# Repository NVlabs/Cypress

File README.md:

# Cypress: VLSI-Inspired Scalable GPU-Accelerated PCB Placement

Cypress is a scalable, GPU-accelerated PCB placement method inspired by VLSI. It incorporates
tailored cost functions, constraint handling, and optimized techniques adapted for PCB layouts.

## How to Build

You can build in two ways:

- Build without Docker by following the instructions of the DREAMPlace build at README_DREAMPlace.md.
- Use the provided Dockerfile to build an image with the required library dependencies.

## Run PCB Placement

```sh
cd /Cypress
python dreamplace/Placer.py path/to/your/config.json
```

## Run Hyperparameter search

```sh
./tuner/run_tuner.sh 1 1 	test/tune/pcb-configspace.json 	/path/to/aux_file 	test/tuner/tuner-ppa.json "" 	100 4 0 0 10 	./tuner 	./results/result_path
```

## Acknowledgement

Cypress builds upon and extends the following open-source projects:

- [DREAMPlace](https://github.com/limbo018/DREAMPlace): A deep learning toolkit-enabled VLSI placement framework that provides the foundation for our GPU-accelerated placement engine.

- [AutoDMP](https://github.com/NVlabs/AutoDMP): An automated design methodology platform that inspired aspects of our hyperparameter tuning approach.

We thank the authors and contributors of these projects for their valuable work that made Cypress possible.

## Citation

If you find this work useful, please cite the following paper:

```bibtex
@inproceedings{zhang2025cypress,
  title={Cypress: VLSI-Inspired PCB Placement with GPU Acceleration},
  author={Zhang, Niansong and Agnesina, Anthony and Shbat, Noor and Leader, Yuval and Zhang, Zhiru and Ren, Haoxing},
  booktitle={Proceedings of the 2025 International Symposium on Physical Design},
  pages={xx--xx},
  year={2025}
}
```

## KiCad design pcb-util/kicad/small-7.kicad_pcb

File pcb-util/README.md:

# pcb-util

## Getting started

To make it easy for you to get started with GitLab, here's a list of recommended next steps.

Already a pro? Just edit this README.md and make it your own. Want to make it easy? [Use the template at the bottom](#editing-this-readme)!

## Add your files

- [ ] [Create](https://docs.gitlab.com/ee/user/project/repository/web_editor.html#create-a-file) or [upload](https://docs.gitlab.com/ee/user/project/repository/web_editor.html#upload-a-file) files
- [ ] [Add files using the command line](https://docs.gitlab.com/ee/gitlab-basics/add-file.html#add-a-file-using-the-command-line) or push an existing Git repository with the following command:

```
cd existing_repo
git remote add origin https://gitlab-master.nvidia.com/niansongz/pcb-util.git
git branch -M main
git push -uf origin main
```

## Integrate with your tools

- [ ] [Set up project integrations](https://gitlab-master.nvidia.com/niansongz/pcb-util/-/settings/integrations)

## Collaborate with your team

- [ ] [Invite team members and collaborators](https://docs.gitlab.com/ee/user/project/members/)
- [ ] [Create a new merge request](https://docs.gitlab.com/ee/user/project/merge_requests/creating_merge_requests.html)
- [ ] [Automatically close issues from merge requests](https://docs.gitlab.com/ee/user/project/issues/managing_issues.html#closing-issues-automatically)
- [ ] [Enable merge request approvals](https://docs.gitlab.com/ee/user/project/merge_requests/approvals/)
- [ ] [Set auto-merge](https://docs.gitlab.com/ee/user/project/merge_requests/merge_when_pipeline_succeeds.html)

## Test and Deploy

Use the built-in continuous integration in GitLab.

- [ ] [Get started with GitLab CI/CD](https://docs.gitlab.com/ee/ci/quick_start/index.html)
- [ ] [Analyze your code for known vulnerabilities with Static Application Security Testing (SAST)](https://docs.gitlab.com/ee/user/application_security/sast/)
- [ ] [Deploy to Kubernetes, Amazon EC2, or Amazon ECS using Auto Deploy](https://docs.gitlab.com/ee/topics/autodevops/requirements.html)
- [ ] [Use pull-based deployments for improved Kubernetes management](https://docs.gitlab.com/ee/user/clusters/agent/)
- [ ] [Set up protected environments](https://docs.gitlab.com/ee/ci/environments/protected_environments.html)

***

# Editing this README

When you're ready to make this README your own, just edit this file and use the handy template below (or feel free to structure it however you want - this is just a starting point!). Thanks to [makeareadme.com](https://www.makeareadme.com/) for this template.

## Suggestions for a good README

Every project is different, so consider which of these sections apply to yours. The sections used in the template are suggestions for most open source projects. Also keep in mind that while a README can be too long and detailed, too long is better than too short. If you think your README is too long, consider utilizing another form of documentation rather than cutting out information.

## Name
Choose a self-explaining name for your project.

## Description
Let people know what your project can do specifically. Provide context and add a link to any reference visitors might be unfamiliar with. A list of Features or a Background subsection can also be added here. If there are alternatives to your project, this is a good place to list differentiating factors.

## Badges
On some READMEs, you may see small images that convey metadata, such as whether or not all the tests are passing for the project. You can use Shields to add some to your README. Many services also have instructions for adding a badge.

## Visuals
Depending on what you are making, it can be a good idea to include screenshots or even a video (you'll frequently see GIFs rather than actual videos). Tools like ttygif can help, but check out Asciinema for a more sophisticated method.

## Installation
Within a particular ecosystem, there may be a common way of installing things, such as using Yarn, NuGet, or Homebrew. However, consider the possibility that whoever is reading your README is a novice and would like more guidance. Listing specific steps helps remove ambiguity and gets people to using your project as quickly as possible. If it only runs in a specific context like a particular programming language version or operating system or has dependencies that have to be installed manually, also add a Requirements subsection.

## Usage
Use examples liberally, and show the expected output if you can. It's helpful to have inline the smallest example of usage that you can demonstrate, while providing links to more sophisticated examples if they are too long to reasonably include in the README.

## Support
Tell people where they can go to for help. It can be any combination of an issue tracker, a chat room, an email address, etc.

## Roadmap
If you have ideas for releases in the future, it is a good idea to list them in the README.

## Contributing
State if you are open to contributions and what your requirements are for accepting them.

For people who want to make changes to your project, it's helpful to have some documentation on how to get started. Perhaps there is a script that they should run or some environment variables that they need to set. Make these steps explicit. These instructions could also be useful to your future self.

You can also document commands to lint the code or run tests. These steps help to ensure high code quality and reduce the likelihood that the changes inadvertently break something. Having instructions for running tests is especially helpful if it requires external setup, such as starting a Selenium server for testing in a browser.

## Authors and acknowledgment
Show your appreciation to those who have contributed to the project.

## License
For open source projects, say how it is licensed.

## Project status
If you have run out of energy or time for your project, put a note at the top of the README saying that development has slowed down or stopped completely. Someone may choose to fork your project or volunteer to step in as a maintainer or owner, allowing your project to keep going. You can also make an explicit request for maintainers.

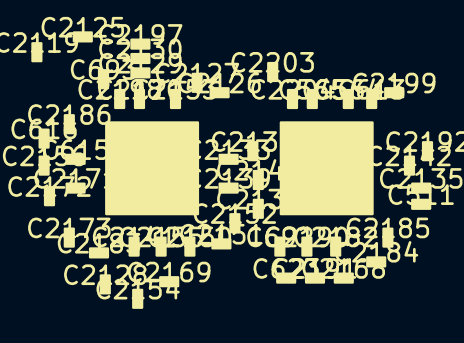
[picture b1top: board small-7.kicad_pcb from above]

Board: 2 copper layers, 52 parts (0 on the bottom side), 44 nets, no tracks yet.

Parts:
C448: C448
C449: C449
C511: C511
C564: C564
C565: C565
C613: C613
C615: C615
C616: C616
C623: C623
C692: C692
C693: C693
C2119: C2119
C2125: C2125
C2126: C2126
C2127: C2127
C2128: C2128
C2129: C2129
C2130: C2130
C2133: C2133
C2134: C2134
C2135: C2135
C2138: C2138
C2139: C2139
C2140: C2140
C2141: C2141
C2142: C2142
C2150: C2150
C2151: C2151
C2152: C2152
C2153: C2153
C2154: C2154
C2155: C2155
C2156: C2156
C2168: C2168
C2169: C2169
C2170: C2170
C2171: C2171
C2172: C2172
C2173: C2173
C2182: C2182
C2183: C2183
C2184: C2184
C2185: C2185
C2186: C2186
C2190: C2190
C2191: C2191
C2192: C2192
C2197: C2197
C2198: C2198
C2199: C2199
C2203: C2203
C2204: C2204

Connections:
N45: C448.0, C448.1, C449.0, C449.1, C564.0, C565.0, C2119.0, C2125.0, C2129.0, C2153.0, C2170.0, C2198.0, C2204.0
N73: C449.2, C2197.0, C2198.1
N74: C448.2, C2203.0, C2204.1
N431: C449.3, C615.1
N452: C449.4, C616.1
N456: C448.3, C613.1
N501: C448.4, C449.5, C2129.1, C2130.1
N526: C448.5, C2199.1
N528: C448.6, C2192.1
N536: C448.7, C2142.1
N538: C448.8, C2135.1
N1836: C448.9, C449.6, C2125.1
N1837: C448.10, C449.7, C2119.1
N4122: C449.9, C2128.1
N4129: C448.22, C511.1
N4139: C449.10, C2155.1
N4163: C449.11, C2169.1
N4172: C449.12, C2171.1
N4179: C449.13, C2156.1
N4187: C449.14, C2154.1
N4196: C449.15, C2141.1
N4213: C449.16, C693.1
N4215: C448.23, C692.1
N4231: C449.17, C2186.1
N4233: C448.24, C623.1
N4244: C448.25, C2191.1
N4247: C448.26, C2185.1
N4250: C448.27, C2168.1
N4258: C448.28, C2190.1
N4261: C448.29, C2184.1
N4264: C448.30, C2182.1
N4303: C449.18, C2133.1
N4308: C449.19, C2151.1
N4313: C449.20, C2140.1
N4318: C449.21, C2150.1
N4383: C449.22, C2126.1
N4388: C449.23, C2138.1
N4393: C449.24, C2134.1
N4398: C449.25, C2152.1
N4427: C449.26, C2183.0
N4586: C449.27, C2127.1
N4591: C449.28, C2139.1
N4651: C449.29, C2173.1
N4660: C449.30, C2172.1

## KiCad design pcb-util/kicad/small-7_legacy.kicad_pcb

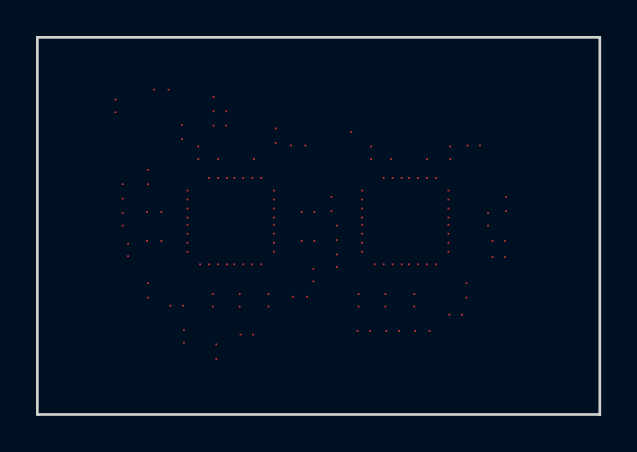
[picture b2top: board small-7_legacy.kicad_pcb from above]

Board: 2 copper layers, 31.2 x 21.0 mm, 52 parts (0 on the bottom side), 44 nets, no tracks yet.

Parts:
C0: C0; C2153
C1: C1; C2170
C2: C2; C564
C3: C3; C565
C4: C4; C693
C5: C5; C2186
C6: C6; C2173
C7: C7; C2172
C8: C8; C2171
C9: C9; C2156
C10: C10; C2155
C11: C11; C2154
C12: C12; C2141
C13: C13; C2128
C14: C14; C615
C15: C15; C616
C16: C16; C623
C17: C17; C692
C18: C18; C613
C19: C19; C511
C20: C20; C2204
C21: C21; C2203
C22: C22; C2198
C23: C23; C2197
C24: C24; C2125
C25: C25; C2119
C26: C26; C2130
C27: C27; C2129
C28: C28; C2199
C29: C29; C2192
C30: C30; C2142
C31: C31; C2135
C32: C32; C2169
C33: C33; C2168
C34: C34; C2182
C35: C35; C2127
C36: C36; C2126
C37: C37; C2134
C38: C38; C2133
C39: C39; C2140
C40: C40; C2139
C41: C41; C2138
C42: C42; C2152
C43: C43; C2151
C44: C44; C2150
C45: C45; C2185
C46: C46; C2184
C47: C47; C2183
C48: C48; C2191
C49: C49; C2190
C50: C50; C448
C51: C51; C449

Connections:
N45: C0.0, C1.0, C2.0, C3.0, C20.0, C22.0, C24.0, C25.0, C27.0, C50.0, C50.1, C51.0, C51.1
N73: C22.1, C23.0, C51.2
N74: C20.1, C21.0, C50.2
N431: C14.1, C51.3
N452: C15.1, C51.4
N456: C18.1, C50.3
N501: C26.1, C27.1, C50.4, C51.5
N526: C28.1, C50.5
N528: C29.1, C50.6
N536: C30.1, C50.7
N538: C31.1, C50.8
N1836: C24.1, C50.9, C51.6
N1837: C25.1, C50.10, C51.7
N4122: C13.1, C51.9
N4129: C19.1, C50.22
N4139: C10.1, C51.10
N4163: C32.1, C51.11
N4172: C8.1, C51.12
N4179: C9.1, C51.13
N4187: C11.1, C51.14
N4196: C12.1, C51.15
N4213: C4.1, C51.16
N4215: C17.1, C50.23
N4231: C5.1, C51.17
N4233: C16.1, C50.24
N4244: C48.1, C50.25
N4247: C45.1, C50.26
N4250: C33.1, C50.27
N4258: C49.1, C50.28
N4261: C46.1, C50.29
N4264: C34.1, C50.30
N4303: C38.1, C51.18
N4308: C43.1, C51.19
N4313: C39.1, C51.20
N4318: C44.1, C51.21
N4383: C36.1, C51.22
N4388: C41.1, C51.23
N4393: C37.1, C51.24
N4398: C42.1, C51.25
N4427: C47.0, C51.26
N4586: C35.1, C51.27
N4591: C40.1, C51.28
N4651: C6.1, C51.29
N4660: C7.1, C51.30

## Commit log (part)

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2019-10-06 fix boost link in readme
2019-10-15 rename maximum independent set to maximal
2019-10-15 global swap deterministic now
2019-10-17 k reorder deterministic now; found ism is not deterministic for bigblue4
2019-10-19 add run-to-run determinism to readme
2019-10-26 change default install prefix to current_path/install
2019-10-26 clarify the run-to-run determinism is for one machine/device
2019-10-28 add dreamplace flow to readme
2019-10-28 add image
2019-11-05 early release of docker for easier compile environment
2019-11-08 support movable macros with greedy and lp based macro legalization
2019-11-08 update legalization flow figure
2019-11-08 add limits to hannan grid sizes and fix missing read_pl
2019-11-08 fix bug in macro legalization from numeric type in mcf solver and site/row misalignment in hannan grid
2019-11-15 clamp fixed density map and add more detailed debug message to cpu
2019-11-18 use exactly the same impl for fixed density map computation as cpu/cuda
2019-12-08 set numpy threading as well after reading the parameters
2019-12-10 switch to clean control over json parameters and add description to readme as well
2019-12-18 support torch 1.3.1. coauthor: Jiaqi Gu
2019-12-18 add file for rudy and adjust instance area
2019-12-21 coauthor Jiaqi Gu, tmp checkpoint
2019-12-21 fix cmake issue when no cuda available
2019-12-21 fix bug in parsing parameters
2019-12-21 make previous bug fix general to python2 and python3
2019-12-22 the area optimization can run
2019-12-22 recover node size and pin offset for legalization
2019-12-22 fix bug in reading DEF file with UNPLACED instance without ORIENT
2019-12-22 fix DEF writer and diverging issue on ISPD2015 benchmarks by scaling the site width to 1
2019-12-23 fix bug in params to get solution file format
2019-12-23 ispd2005 test JSON adds L2/L3 iterations
2019-12-24 change nonlinear place to 3-level nested problems
2019-12-24 guarantee run-to-run determinism on CPU now
2019-12-24 fix bug when regions are placed after groups in DEF
2019-12-25 track ispd2005 JSON files for adam and momentum solvers
2019-12-26 coauthor: Gu Jiaqi. finish area computations on GPU
2019-12-27 coauthor: Jiaqi Gu. add unittests for pin utilization and rudy
2019-12-28 pass AdjustNodeAreaUnittest
2019-12-28 clean adjust node area and unitest
2019-12-30 tune routability in progress
2019-12-31 weighted average wirelength CPU implementations of atomic and merged
2020-01-01 Add unittest. Improve CPU merged implementation.
2020-01-05 integrate nctugr binary for routing congestion estimation
2020-01-05 change back to call ntuplace4h
2020-01-05 Revert "resolve merge conflict"
    This reverts commit a29376cf3cd48015002ff325e95d718a6a23fe3e, reversing
    changes made to f26a3c230b7f59befb56b5053743d8bf93be6ca6.
2020-01-07 remove redundant if-else in weighted_average_wirelength
2020-01-07 remove wa wl sparse implementation
2020-01-08 remove redundant POST9 and POWV9 files for flute and NCTUgr.ICCAD2012
2020-01-08 move legality check to python operator
2020-01-08 update dac2012 json files
2020-01-08 fix compile warning in wa wl
2020-01-08 fix hard-coded gamma to JSON files
2020-01-17 fix bug in macro legalization
2020-01-19 fix bug in logsumexp wl computation
2020-01-31 add ABCDPlace paper
2020-02-06 fix macro legalization for bigblue3 when there are single-pin macros overlapping with each other
2020-02-07 rearrange code for Robert's mixed-size placement exp
2020-02-13 add a configure file to record the compile information for an installation
2020-02-13 remove depracated wa sparse
2020-03-05 add checking when target density is smaller than utilization
2020-03-18 resolve issue with boost-cmake
2020-03-19 add load function for pklz
2020-03-25 fix bug in global swap for space misalignment
2020-03-28 remove unused dependency to cusparse
2020-03-28 fix failure in regression test of adaptec2
2020-04-14 debug for inconsistent in electric_potential unittest
2020-04-14 sorted node map should only be on the movable nodes
2020-04-15 fix bug in ispd19 benchmarks with multiple sites; hotfix of divergence issue with better preconditioning, which may not be the best way
2020-04-16 separate place_io python binding into multipel files to speedup make
2020-04-17 support parallel building now
2020-04-18 replace buffer-style density map computation with fixed point numbers
2020-04-20 add regression test
2020-04-20 detect divergence and add assertion to fence regions
2020-04-29 handle non-CORE classes in LEF, regard as fixed
2020-04-29 try to match plus for this commit
2020-04-30 add regression test for iccad2014/ispd2014
2020-04-30 return metrics after finishing place for data collection
2020-05-06 fix bug for ispd2018 with numerical precision issues; we cannot legalize test10 yet, as it is too dense
2020-05-06 fix efficiency issue when wildcard matching fence regions
2020-05-07 update benchmark configuration files
2020-05-11 add upper bounds for alpha in preconditioning
2020-05-13 init commit
2020-05-13 update optimizer
2020-05-13 solve prob 2
2020-05-13 recover nonlinearplace.py
2020-05-13 bug fix
2020-05-13 bug fixed
2020-05-13 move out nonexclusive cell
2020-05-13 fix nonexclusive cell
2020-05-13 fence region update
2020-05-13 fence region exclude
2020-05-14 update fence region margin
2020-05-14 update region check
2020-05-16 quadratic and multi-electric field
2020-05-17 multi-electric field
2020-06-11 remove support to python2
2020-06-11 add ispd19 test script
2020-07-07 fix issue with DEF pins without layer and bounding box
2020-07-07 handle DEF net weighting now
2020-07-09 better check on divergence
2020-07-09 fix bug of block count overflow in density map kernel launching
2020-07-12 fix bug in inconsistent lef/def unit
2020-07-13 compile issue after merging
2020-08-10 fix bug in reading verilog modules
2020-08-27 add missing members in PlaceDB
2021-02-23 fix typo in unused build_density_overflow
2021-06-03 Update benchmarks
    Correct README and benchmark Python script
2021-06-15 FFT API compatibility for PyTorch 1.8
2021-06-15 fix CXX standard issue due to wierd cmake initialization to CMAKE_CXX_FLAGS
2021-06-17 update to torch header
2021-06-21 remove setup.py.in and use CMakeLists only
2021-06-23 Fix TARGET_NAME typo in k_reorder and comment rmst_wl
2021-06-25 DP working under PyTorch 1.8 + CUDA 11.\n Major fixes: 1. Put cub into DreamPlace namespace (following https://github.com/dmlc/dgl/pull/2758/commits/fd183c156b063c2c783e0a9d3501bce4a44f9aeb);\n 2. Re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
2021-07-02 set default detailed placer on ISPD 2005 benchmarks to ABCDPlace
2021-07-08 fix bug in cmake of pin_pos
2021-07-22 update docker configuration.
2021-08-23 node2fence region map fix
    Conflicts:
    dreamplace/ops/global_swap/src/global_swap_cuda_kernel.cu
2021-08-23 fence region legalization and legality check
    Conflicts:
    dreamplace/BasicPlace.py
2021-08-23 only abacus after one legality check
2021-08-23 fix precond bug
2021-08-23 add global overflow
2021-08-23 enlarge virtual macro dilation
2021-08-23 enable placement flag for all ispd15 and ispd19
2021-08-23 fix bug in ntuplace4dr call
2021-08-23 fix some tensor shape issue
2021-08-23 fix bug in polygen slicing
2021-08-23 quadratic penalty and alpha increase
2021-08-23 fix merge slicing bug
2021-08-23 fix bug in movable macro mask
2021-08-23 enable blockage for ISPD2015
2021-08-23 fix overflow tensor shape issue
2021-08-23 add dreamplace 2.0 paper
2021-08-28 [dreamplace3.0] update GP flow
2021-08-28 [dreamplace3.0] remove placedb usage in base_gamma
2021-08-28 [dreamplace3.0] fix fence region install bug
2021-08-28 [dreamplace3.0] ispd 2015 regression test script
2021-08-28 [dreamplace3.0] multiple runs to test sensitivity
2021-08-30 [dreamplace3.0] update shapely package
2021-08-30 [dreamplace3.0] clean comments and format
2021-08-31 update readme to include 3.0 features
2021-09-04 update dockerfiler and requirement to torch version and shapely
2022-11-17 fix bug in PlaceDB when calling dreamplacePrint
2022-11-17 fix numerical bug in abacus legalization when distributing cells into rows
2022-11-17 bin num calculate error
    ```math.ceil()``` can cause ```num_bins``` calculation errors.
2022-11-17 add heuristic to select core site when there are multiple site definitions
2022-11-17 AutoDMP dreamplace update
2022-11-17 AutoDMP tuner
2022-11-17 update requirements
2022-11-17 AutoDMP add hpbandster library
2022-11-18 update Dockerfile
2022-11-18 update dockerfile with correct torch installation
2022-11-19 Keep DREAMPlace README
2022-11-19 Fix bug in HPWL x/y summation
2022-11-19 Formatting BOHB
2022-11-19 MOBOHB typo for budgets
2022-11-21 Update REAME
2022-11-21 Update docker instructions
2022-11-22 Paretos extraction
2022-11-23 Update run analysis + revert HPWL net-to-net
2022-11-29 Typo tuner_train
2022-12-05 Remove Overflow computation with OpenCV
2023-03-20 Fix old bug with macro pin offsets
2023-03-21 Update generate bookshelf for proper naming
2023-03-21 Fix RUDY macro demand
2023-03-21 Remove SPDX copyright of non-NVIDIA authored files
2023-03-27 Update Links
2023-04-05 update install CMakeLists for macro ops
2024-07-03 net crossing initial commit
2024-07-03 Use LFS
2024-07-08 Add gradient computation
2024-07-08 Add backward function
2024-07-08 Add net crossing class
2024-07-08 Add NetCrossingFunction
2024-07-08 Various minor fixes
2024-07-09 Fix compilation errors
2024-07-09 Add golden net crossing pytorch version
2024-07-09 Add net crossing test in unit test
2024-07-09 Fix net crossing golden forward
2024-07-09 Fix net crossing golden
2024-07-09 minor fix
2024-07-09 Add build_net_crossing
2024-07-09 Add to PlaceOpCollection
2024-07-09 Integrate net crossing to placer
2024-07-09 Fix backprob for net crossing
2024-07-09 Plot Net Crossing
2024-07-09 net crossing cuda kernel initial commit
2024-07-10 Minor fix for net_crossing_cuda_kernel
2024-07-10 net crossing cuda initial commit
2024-07-10 net crossing cuda compilation successful
2024-07-10 net_crossing python api cuda initial commit
2024-07-10 Minor fix for GPU net crossing, pass unit test
2024-07-10 Use net crossing unit test
2024-07-10 Fix device issue with _lambda, _mu, _sigma
2024-07-10 Add comments
2024-07-16 Fix an issue with unit test
2024-07-17 Report net crossing
2024-07-17 Add net crossing weight
2024-07-17 Add net crossing weight, updating functions
2024-07-18 Reproduce p154 experiment
2024-07-18 Add filler nodes for top/btm WIP
2024-07-18 Fix PlaceObj
2024-07-19 Use total movable macro area for overflow calculation
2024-07-21 Make reproducing easier
2024-07-21 Add pb310-reduced benchmark
2024-07-22 P140 works
2024-07-23 Add P140 benchmark
2024-07-28 Add an example with gumbel softmax
2024-07-28 Check progress
2024-07-29 Add combinational gumbel softmax exmaple
2024-07-29 Add rotation
2024-07-30 Save progress on rotation
2024-08-01 Add a separate optimizer for rotation
2024-08-01 Freeze orientation
2024-08-02 Fix issue with pin pos cuda
2024-08-04 Add small 1
2024-08-05 AutoDMP works
2024-09-03 Fix precond for rotation
2024-09-05 Fixing precond for orient_logits
2024-09-09 Fix issues with gumbel-softmax initialization
2024-09-16 Fix orientation result
2024-09-30 Update RUDY without blockage, fix an issue with net crossing
2024-10-07 Avoid crashing whole search due to memory issue
2024-10-10 Fix the memory issue in AutoDMP
2024-10-14 Update drawplace to allow two sides
2024-10-16 Add test/tune
2024-10-21 Update comments
2024-10-21 Update filler nodes area
2024-10-21 Updating density WIP
2024-10-22 Separate density maps
2024-10-23 Skip density map if any side is empty
2024-10-23 Use two side functions for density eval
2024-10-24 Side-aware NetCrossing
2024-10-28 Fix issues with macro overlap two sides
2024-10-29 remove old benchmarks
2024-10-29 Remove benchmark dir from CMakeList
2024-10-31 Legalize flag turn on in tuner_config.py
2024-10-31 Update docker file
2024-10-31 Add DCO language
2024-12-02 adding pcb-util
2024-12-18 KiCAD4 converter WIP
2024-12-30 Add ns-place results converted to bookshelf
2024-12-30 Add third party files
2025-03-12 Update latest commits
